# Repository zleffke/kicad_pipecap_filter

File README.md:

# kicad_pipecap_filter
Pipe Cap RF Cavity Filters

## Filters
- pcf_0.5in: 1/2" pipe cap filter.
- pcf_0.75in: 3/4" pipe cap filter.
- pcf_1.0in: 1" pipe cap filter.

### Credit where its due!
This project is heavily inspired by the awesome work of Paul Wade, W1GHZ.  
This is my attempt to recreate some of his work with my own PCB layouts.  
For much better solutions than anything I'm likely to come up with, I highly recommend you check out Paul's website:
- [W1GHZ Filter Articles](http://www.w1ghz.org/filter/Filter_articles.htm)
- [W1GHZ Transverters](http://www.w1ghz.org/xvtr/transverter.htm)
- [W1GHZ Main Page](http://www.w1ghz.org/)

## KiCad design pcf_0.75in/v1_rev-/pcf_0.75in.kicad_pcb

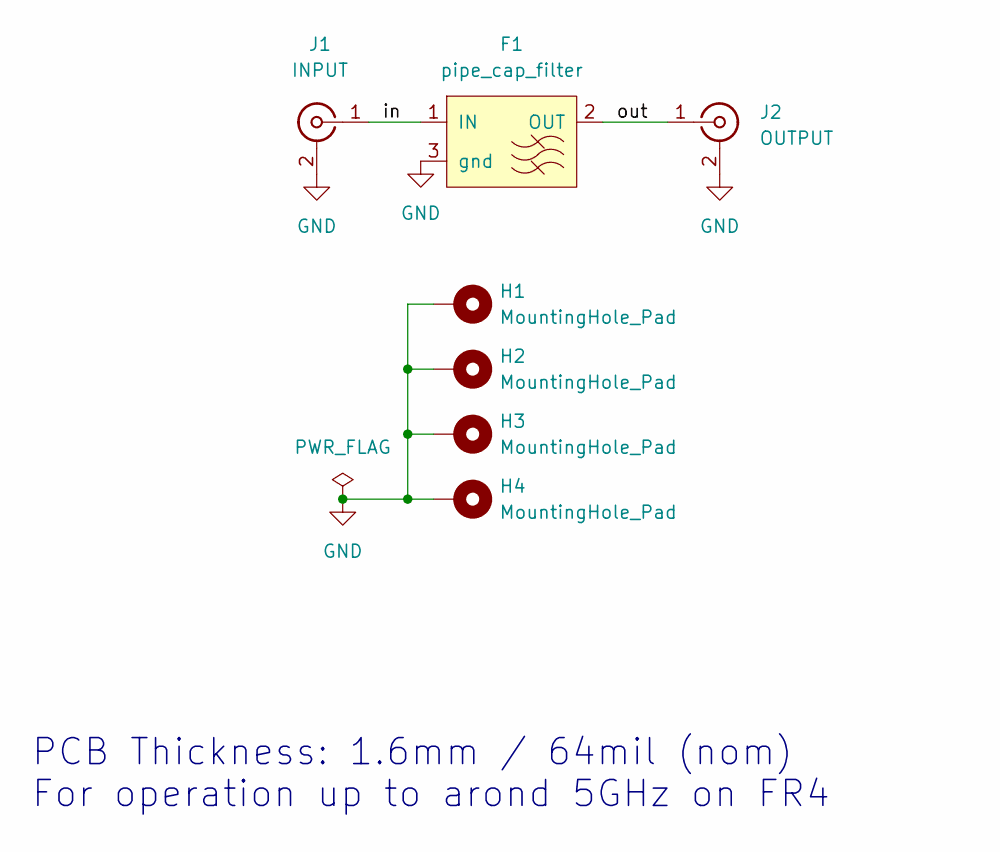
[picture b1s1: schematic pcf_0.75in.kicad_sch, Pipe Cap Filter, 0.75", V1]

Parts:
F1: pipe_cap_filter
H1, H2, H3: MountingHole_Pad; MountingHole_3.2mm_M3_DIN965_Pad
H4: MountingHole_Pad; MountingHole_3.2mm_M3_ISO7380_Pad
J1: INPUT; TAOGLAS_EMPCB.SMAFSTJ.B.HT
J2: OUTPUT; TAOGLAS_EMPCB.SMAFSTJ.B.HT

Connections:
/in: F1.1 (IN), J1.1 (In)
/out: F1.2 (OUT), J2.1 (In)
GND: F1.3 (gnd), H1.1, H2.1, H3.1, H4.1, J1.2 (Ext), J2.2 (Ext)

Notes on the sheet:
PCB Thickness: 1.6mm / 64mil (nom) For operation up to arond 5GHz on FR4

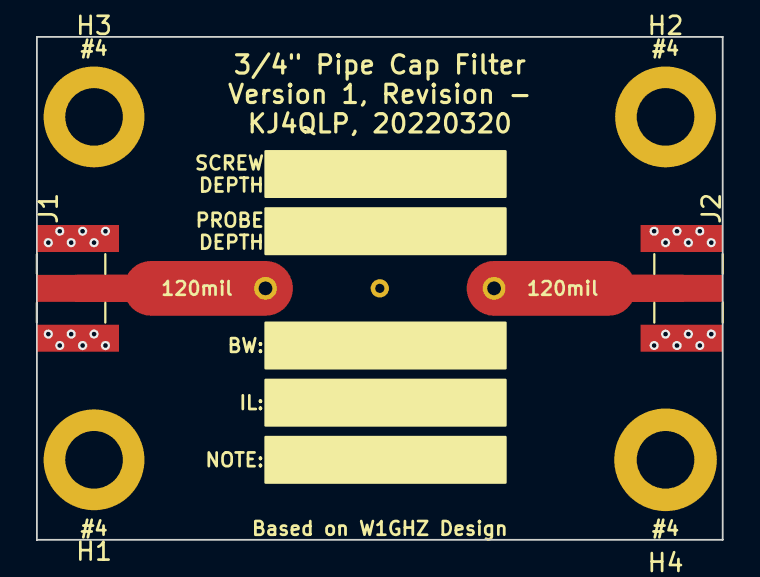
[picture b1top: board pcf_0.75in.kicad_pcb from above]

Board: 2 copper layers, 38.1 x 27.9 mm, 7 parts (0 on the bottom side), 3 nets.

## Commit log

2022-03-21 initial commit of 1/2" filters. Sent to osh park 20220320
2022-03-21 initial commit of 0.75in pipe cap filter board.

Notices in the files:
pcf_0.75in/v1_rev-/pcf_0.75in.kicad_pcb:
creativecommons.org/licenses/by/4.0
License: CC BY 4.0
